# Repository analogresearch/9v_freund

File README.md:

# 9V for your Eurorack

9V Spannungsregler der direkt in eine Eurorack busbar passt. Max 1A. Polung beachten!

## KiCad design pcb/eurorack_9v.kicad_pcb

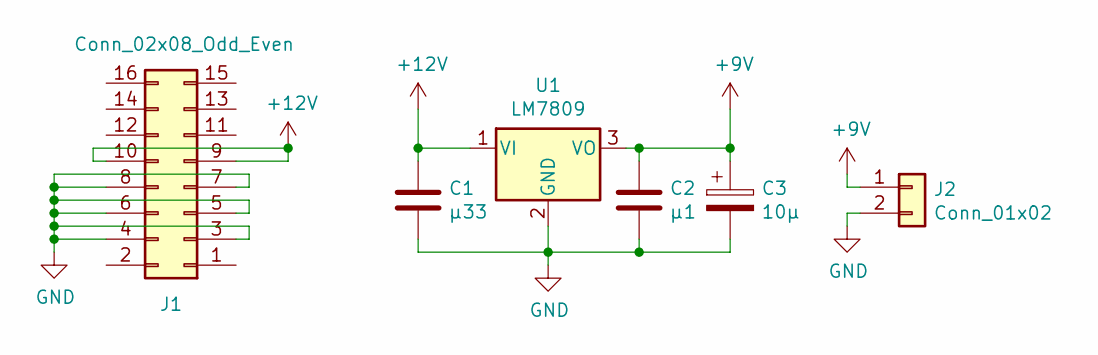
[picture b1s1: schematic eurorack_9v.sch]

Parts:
C1: µ33; C_1206_3216Metric
C2: µ1; C_1206_3216Metric
C3: 10µ; C_1206_3216Metric
J1: Conn_02x08_Odd_Even; PinSocket_2x08_P2.54mm_Horizontal
J2: Conn_01x02; EK508V-02P
U1: LM7809; TO-263-3_TabPin4

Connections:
+9V: C2.1, C3.1, J2.1, U1.3 (VO)
+12V: C1.1, J1.9, J1.10, U1.1 (VI)
GND: C1.2, C2.2, C3.2, J1.3, J1.4, J1.5, J1.6, J1.7, J1.8, J2.2, U1.2 (GND)

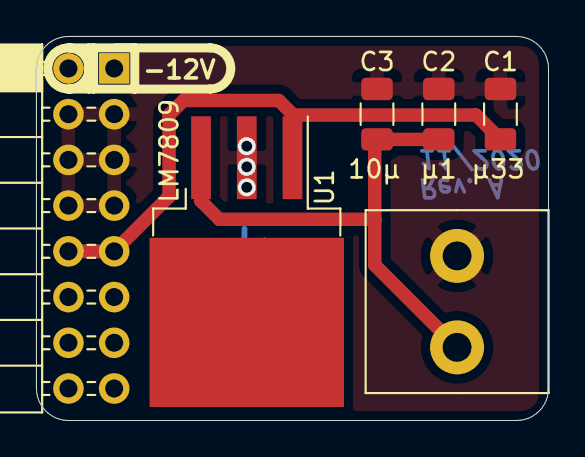
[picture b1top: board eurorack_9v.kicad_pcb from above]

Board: 2 copper layers, 28.4 x 21.3 mm, 7 parts (1 on the bottom side), 3 nets.

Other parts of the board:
Ref**: Val**; logo-analogresearch-10mm

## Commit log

2020-12-02 inital commit
2020-12-02 added pcb layout
2020-12-02 bugfix README.md
